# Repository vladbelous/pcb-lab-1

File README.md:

## PCB Lab #1 - Level Shifting

"Lab"-style PCB for experimenting with different voltage level shifting
solutions, as well as battery voltage measurement and reporting in a multi-voltage system.

TODO: add more description

## Schematic:

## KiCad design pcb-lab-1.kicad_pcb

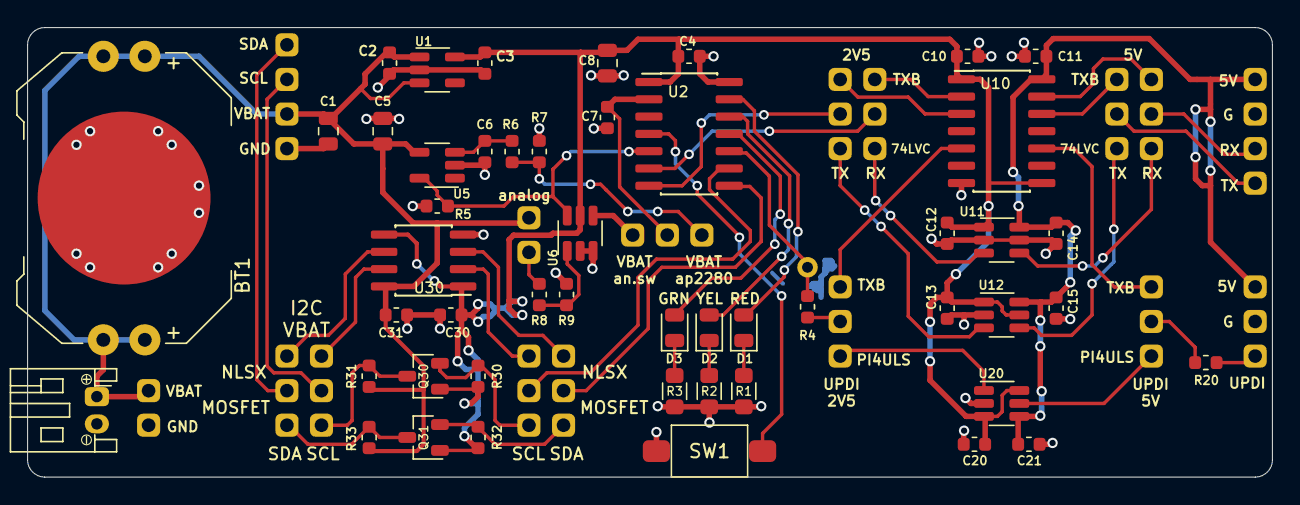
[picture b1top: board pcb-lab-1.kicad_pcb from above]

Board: 2 copper layers, 91.4 x 33.0 mm, 66 parts (0 on the bottom side), 50 nets.

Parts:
BT1: CR2032; CR2032_Holder_Linx
C1: 10u; C_0805_2012Metric
C2, C3, C4, C6, C7, C10, C11, C12, C13, C14, C15, C20, C21, C30, C31: 100n; C_0603_1608Metric
C5, C8: 1u; C_0805_2012Metric
D1: RED; LED_0805_2012Metric
D2: YEL; LED_0805_2012Metric
D3: GRN; LED_0805_2012Metric
J1: BAT; Pin_Header_Straight_1x02_Pitch2.54mm
J2: UPDI_PIN_SMD; Conn_1-wire
J10, J14: JP_RX; Pin_Header_Straight_1x03_Pitch2.54mm
J11, J15: JP_TX; Pin_Header_Straight_1x03_Pitch2.54mm
J18: UART; Pin_Header_Straight_1x04_Pitch2.54mm
J20: UPDI; Pin_Header_Straight_1x03_Pitch2.54mm
JD1: I2C display; Pin_Header_Straight_1x04_Pitch2.54mm
JP1: jumper; Pin_Header_Straight_1x02_Pitch2.54mm
JP2: ADC; Pin_Header_Straight_1x03_Pitch2.54mm
JP20, JP21: UPDI; Pin_Header_Straight_1x03_Pitch2.54mm
JP30, JP32: SCL; Pin_Header_Straight_1x03_Pitch2.54mm
JP31, JP33: SDA; Pin_Header_Straight_1x03_Pitch2.54mm
JST_PH_BAT1: JST_PH_BAT; JST_PH_S2B-PH-K_02x2.00mm_Angled_WiderHole
Q30, Q31: NMOS_GSD; SOT-23_HS
R1, R2, R3: 1k; 0805_HS
R4, R20: 3.3k; R_0603_1608Metric
R5, R6, R7, R30, R31, R32, R33: 10k; R_0603_1608Metric
R8, R9: 100k; R_0603_1608Metric
SW1: BTN; SW_SPST_PUSH_6mm_3mm
U1: AP7354; SOT-23-5_HS
U2: attiny1614; SOIC-14_3.9x8.7mm_Pitch1.27mm_HS
U5: AP2280; SOT-23-5_HS
U6: 74LVC1G3157; SOT-23-6_HS
U10: TXB0104; SOIC-14_3.9x8.7mm_Pitch1.27mm_HS
U11, U12: 74LVC1T45-SOT23-6; SOT-23-6_HS
U20: PI4ULS5V201-SOT23-6; SOT-23-6_HS
U30: NLSX4373; SOIC-8_3.9x4.9mm_Pitch1.27mm_HS

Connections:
2V5: C3.1, C4.1, C8.1, C10.1, C12.1, C13.1, C20.1, C30.1, Q30.1, Q31.1, R30.1, R32.1, U1.5, U2.1, U6.5, U10.1, U10.8, U11.1, U12.1, U12.5, U20.3, U20.6, U30.1, U30.5
5V: C11.1, C14.1, C15.1, C21.1, J18.1, J20.1, U10.14, U11.6, U12.6, U20.4
GND: BT1.2, C1.2, C2.2, C3.2, C4.2, C5.2, C6.2, C7.2, C8.2, C10.2, C11.2, C12.2, C13.2, C14.2, C15.2, C20.2, C21.2, C30.2, C31.2, J1.2, J18.2, J20.2, JD1.4, JST_PH_BAT1.2, R1.1, R2.1, R3.1, R5.2, R7.2, R9.2, SW1.1, U1.2, U2.14, U5.2, U6.2, U6.3, U10.7, U11.2, U11.5, U12.2, U20.2, U30.4
unnamed: C6.1, R6.1, U5.3
unnamed: D1.1, R1.2
unnamed: D1.2, U2.13
unnamed: D2.1, R2.2
unnamed: D2.2, U2.12
unnamed: D3.1, R3.2
unnamed: D3.2, U2.11
unnamed: J2.1, R4.1, U2.10
unnamed: J20.3, R20.2
unnamed: JP1.2, R8.1
unnamed: R8.2, R9.1, U6.1
unnamed: SW1.2, U2.4
RX: J14.2, J18.3
RX_2V5: J10.2, U2.6
RX_2V5_A: J10.1, U10.2
RX_2V5_B: J10.3, U11.3
RX_A: J14.1, U10.13
RX_B: J14.3, U11.4
SCL: JD1.2, JP32.2
SCL_2V5: JP30.2, U2.9
SCL_2V5_A: JP30.1, U30.2
SCL_2V5_B: JP30.3, Q30.2, R30.2
SCL_A: JP32.1, U30.7
SCL_B: JP32.3, Q30.3, R31.2
SDA: JD1.1, JP33.2
SDA_2V5: JP31.2, U2.8
SDA_2V5_A: JP31.1, U30.3
SDA_2V5_B: JP31.3, Q31.2, R32.2
SDA_A: JP33.1, U30.6
SDA_B: JP33.3, Q31.3, R33.2
TX: J15.2, J18.4
TX_2V5: J11.2, U2.7
TX_2V5_A: J11.1, U10.3
TX_2V5_B: J11.3, U12.3
TX_A: J15.1, U10.12
TX_B: J15.3, U12.4
UPDI: JP21.2, R20.1
UPDI_2V5: JP20.2, R4.2
UPDI_2V5_A: JP20.1, U10.5
UPDI_2V5_B: JP20.3, U20.1
UPDI_A: JP21.1, U10.10
UPDI_B: JP21.3, U20.5
VBAT: BT1.1, C1.1, C2.1, C5.1, C31.1, J1.1, JD1.3, JP1.1, JST_PH_BAT1.1, R31.1, R33.1, U1.1, U1.3, U5.4, U30.8
VBAT_ADC: C7.1, JP2.2, U2.2
VBAT_ADC_A: JP2.1, R6.2, R7.1
VBAT_ADC_B: JP2.3, U6.4
VCTRL: R5.1, U2.5, U5.5, U6.6

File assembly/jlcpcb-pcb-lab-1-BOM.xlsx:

Designator | Footprint | Quantity | Value | LCSC Part #
C1 | 805 | 1 | 10u | C15850
C2,C3,C4,C6,C7,C10,C11,C12,C13,C14,C15,C20,C21,C30,C31 | 603 | 15 | 100n | C14663
C5,C8 | 805 | 2 | 1u | C28323
D1 | LED_0805 | 1 | RED | C84256
D2 | LED_0805 | 1 | YEL | C2296
D3 | LED_0805 | 1 | GRN | C2297
Q30,Q31 | SOT-23-3 | 2 | NMOS_GSD | C8545
R1,R2,R3 | 805 | 3 | 1k | C17513
R4,R20 | 603 | 2 | 3.3k | C22978
R5,R6,R7,R30,R31,R32,R33 | 603 | 7 | 10k | C25804
R8,R9 | 603 | 2 | 100k | C25803

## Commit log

2020-05-26 Project init
2020-05-26 Roughly place major components
2020-05-30 Add NLSX4373 symbol
2020-05-30 Schematic ~50%: I2C shifting and UART (except Si8422)
2020-05-30 Add UPDI; fixes
2020-05-30 Remove Si8422 - bad supply range
2020-05-31 Add AP2280 and VBAT measurement circuit
2020-06-01 Add LEDs, button, etc. Finished schematic
2020-06-01 Annotate schematic
2020-06-01 New footprint (CR2032), symbol->footprint assignment
2020-06-01 Layout: initial component arrangement
2020-06-01 Component arrangement
2020-06-06 Add analog switch as option for VBAT
2020-06-06 New netlist, and approx pcb arrangement
2020-06-12 New component arrangement
2020-06-12 VBAT and I2C routing
2020-06-13 Complete routing
2020-06-13 Gerber test; Adjust silkscreen
2020-06-13 Silkscreen
2020-06-13 Gerbers; JLCPCB-friendly BOM and pick-and-place
2020-06-22 Add README
2020-06-29 Add schematic PDF and png

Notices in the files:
pcb-lab-1.kicad_pcb:
CC BY-SA 4.0
